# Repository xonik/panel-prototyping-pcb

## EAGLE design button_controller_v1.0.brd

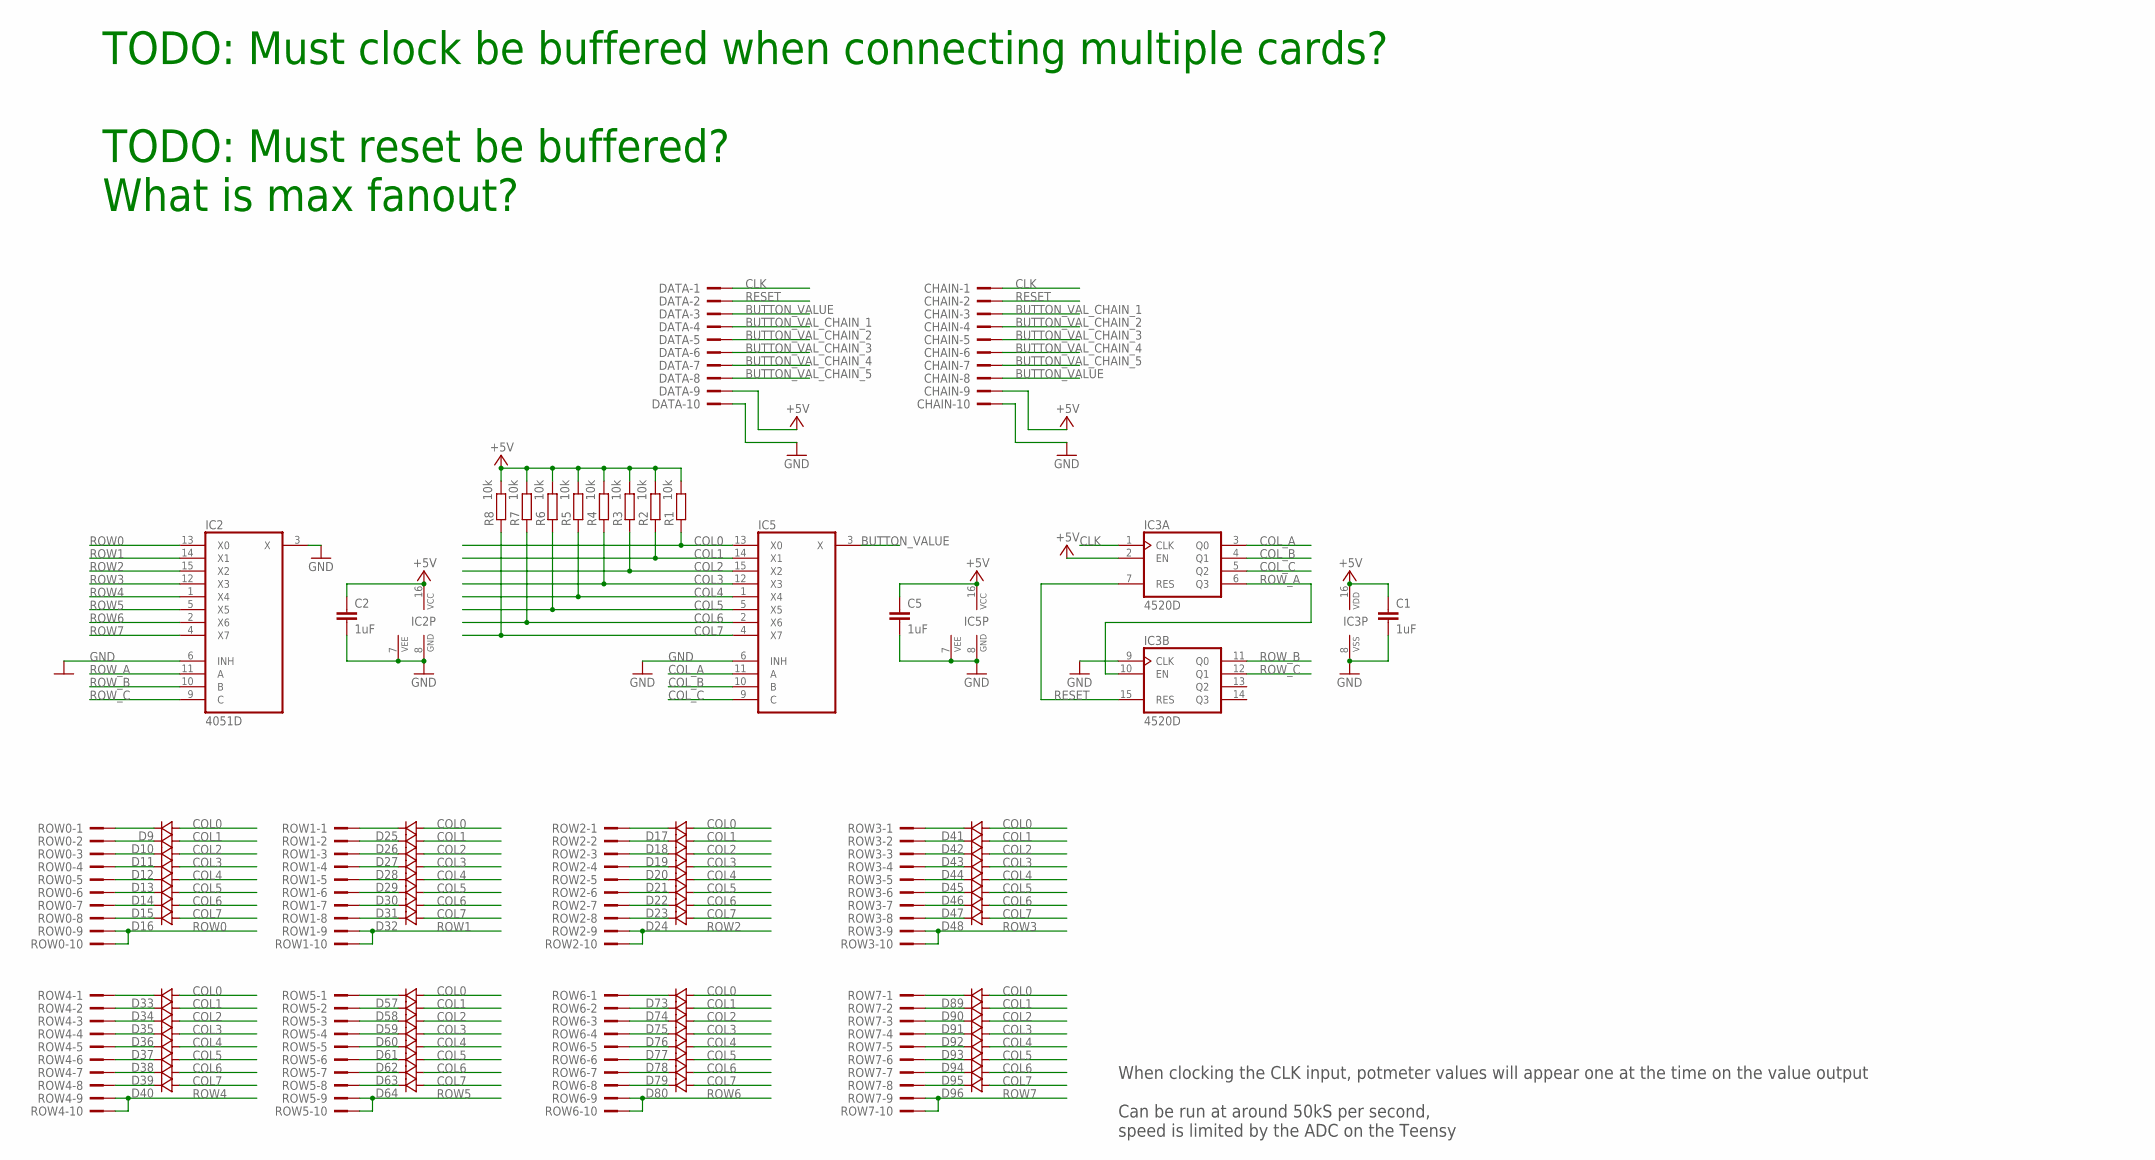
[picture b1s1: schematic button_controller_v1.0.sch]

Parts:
C1, C2, C5: 1uF; C0603-J
CHAIN: CONN-IDC-10PS; CONN-IDC10P-S
D9, D10, D11, D12, D13, D14, D15, D16, D17, D18, D19, D20, D21, D22, D23, D24, D25, D26, D27, D28, D29, D30, D31, D32, D33, D34, D35, D36, D37, D38, D39, D40, D41, D42, D43, D44, D45, D46, D47, D48, D57, D58, D59, D60, D61, D62, D63, D64, D73, D74, D75, D76, D77, D78, D79, D80, D89, D90, D91, D92, D93, D94, D95, D96: 1N4148SOD323; SOD323J
DATA: CONN-IDC-10PS; CONN-IDC10P-S
IC2, IC5: 4051D; SO16
IC3: 4520D; SO16
R1, R2, R3, R4, R5, R6, R7, R8: 10k; R0603
ROW0, ROW1, ROW2, ROW3, ROW4, ROW5, ROW6, ROW7: CONN-IDC-10PS; CONN-IDC10P-S

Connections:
+5V: C1.1, C2.1, C5.1, CHAIN.9, DATA.9, IC2.16 (VCC), IC3.2 (EN), IC3.16 (VDD), IC5.16 (VCC), R1.2, R2.2, R3.2, R4.2, R5.2, R6.2, R7.2, R8.2
BUTTON_VALUE: CHAIN.8, DATA.3, IC5.3 (X)
BUTTON_VAL_CHAIN_1: CHAIN.3, DATA.4
BUTTON_VAL_CHAIN_2: CHAIN.4, DATA.5
BUTTON_VAL_CHAIN_3: CHAIN.5, DATA.6
BUTTON_VAL_CHAIN_4: CHAIN.6, DATA.7
BUTTON_VAL_CHAIN_5: CHAIN.7, DATA.8
CLK: CHAIN.1, DATA.1, IC3.1 (CLK)
COL0: D9.2 (A), D17.2 (A), D25.2 (A), D33.2 (A), D41.2 (A), D57.2 (A), D73.2 (A), D89.2 (A), IC5.13 (X0), R1.1
COL1: D10.2 (A), D18.2 (A), D26.2 (A), D34.2 (A), D42.2 (A), D58.2 (A), D74.2 (A), D90.2 (A), IC5.14 (X1), R2.1
COL2: D11.2 (A), D19.2 (A), D27.2 (A), D35.2 (A), D43.2 (A), D59.2 (A), D75.2 (A), D91.2 (A), IC5.15 (X2), R3.1
COL3: D12.2 (A), D20.2 (A), D28.2 (A), D36.2 (A), D44.2 (A), D60.2 (A), D76.2 (A), D92.2 (A), IC5.12 (X3), R4.1
COL4: D13.2 (A), D21.2 (A), D29.2 (A), D37.2 (A), D45.2 (A), D61.2 (A), D77.2 (A), D93.2 (A), IC5.1 (X4), R5.1
COL5: D14.2 (A), D22.2 (A), D30.2 (A), D38.2 (A), D46.2 (A), D62.2 (A), D78.2 (A), D94.2 (A), IC5.5 (X5), R6.1
COL6: D15.2 (A), D23.2 (A), D31.2 (A), D39.2 (A), D47.2 (A), D63.2 (A), D79.2 (A), D95.2 (A), IC5.2 (X6), R7.1
COL7: D16.2 (A), D24.2 (A), D32.2 (A), D40.2 (A), D48.2 (A), D64.2 (A), D80.2 (A), D96.2 (A), IC5.4 (X7), R8.1
COL_A: IC3.3 (Q0), IC5.11 (A)
COL_B: IC3.4 (Q1), IC5.10 (B)
COL_C: IC3.5 (Q2), IC5.9 (C)
GND: C1.2, C2.2, C5.2, CHAIN.10, DATA.10, IC2.3 (X), IC2.6 (INH), IC2.7 (VEE), IC2.8 (GND), IC3.8 (VSS), IC3.9 (CLK), IC5.6 (INH), IC5.7 (VEE), IC5.8 (GND)
unnamed: D9.1 (C), ROW0.1
unnamed: D10.1 (C), ROW0.2
unnamed: D11.1 (C), ROW0.3
unnamed: D12.1 (C), ROW0.4
unnamed: D13.1 (C), ROW0.5
unnamed: D14.1 (C), ROW0.6
unnamed: D15.1 (C), ROW0.7
unnamed: D16.1 (C), ROW0.8
unnamed: D17.1 (C), ROW2.1
unnamed: D18.1 (C), ROW2.2
unnamed: D19.1 (C), ROW2.3
unnamed: D20.1 (C), ROW2.4
unnamed: D21.1 (C), ROW2.5
unnamed: D22.1 (C), ROW2.6
unnamed: D23.1 (C), ROW2.7
unnamed: D24.1 (C), ROW2.8
unnamed: D25.1 (C), ROW1.1
unnamed: D26.1 (C), ROW1.2
unnamed: D27.1 (C), ROW1.3
unnamed: D28.1 (C), ROW1.4
unnamed: D29.1 (C), ROW1.5
unnamed: D30.1 (C), ROW1.6
unnamed: D31.1 (C), ROW1.7
unnamed: D32.1 (C), ROW1.8
unnamed: D33.1 (C), ROW4.1
unnamed: D34.1 (C), ROW4.2
unnamed: D35.1 (C), ROW4.3
unnamed: D36.1 (C), ROW4.4
unnamed: D37.1 (C), ROW4.5
unnamed: D38.1 (C), ROW4.6
unnamed: D39.1 (C), ROW4.7
unnamed: D40.1 (C), ROW4.8
unnamed: D41.1 (C), ROW3.1
unnamed: D42.1 (C), ROW3.2
unnamed: D43.1 (C), ROW3.3
unnamed: D44.1 (C), ROW3.4
unnamed: D45.1 (C), ROW3.5
unnamed: D46.1 (C), ROW3.6
unnamed: D47.1 (C), ROW3.7
unnamed: D48.1 (C), ROW3.8
unnamed: D57.1 (C), ROW5.1
unnamed: D58.1 (C), ROW5.2
unnamed: D59.1 (C), ROW5.3
unnamed: D60.1 (C), ROW5.4
unnamed: D61.1 (C), ROW5.5
unnamed: D62.1 (C), ROW5.6
unnamed: D63.1 (C), ROW5.7
unnamed: D64.1 (C), ROW5.8
unnamed: D73.1 (C), ROW6.1
unnamed: D74.1 (C), ROW6.2
unnamed: D75.1 (C), ROW6.3
unnamed: D76.1 (C), ROW6.4
unnamed: D77.1 (C), ROW6.5
unnamed: D78.1 (C), ROW6.6
unnamed: D79.1 (C), ROW6.7
unnamed: D80.1 (C), ROW6.8
unnamed: D89.1 (C), ROW7.1
unnamed: D90.1 (C), ROW7.2
unnamed: D91.1 (C), ROW7.3
unnamed: D92.1 (C), ROW7.4
unnamed: D93.1 (C), ROW7.5
unnamed: D94.1 (C), ROW7.6
unnamed: D95.1 (C), ROW7.7
unnamed: D96.1 (C), ROW7.8
RESET: CHAIN.2, DATA.2, IC3.7 (RES), IC3.15 (RES)
ROW0: IC2.13 (X0), ROW0.9, ROW0.10
ROW1: IC2.14 (X1), ROW1.9, ROW1.10
ROW2: IC2.15 (X2), ROW2.9, ROW2.10
ROW3: IC2.12 (X3), ROW3.9, ROW3.10
ROW4: IC2.1 (X4), ROW4.9, ROW4.10
ROW5: IC2.5 (X5), ROW5.9, ROW5.10
ROW6: IC2.2 (X6), ROW6.9, ROW6.10
ROW7: IC2.4 (X7), ROW7.9, ROW7.10
ROW_A: IC2.11 (A), IC3.6 (Q3), IC3.10 (EN)
ROW_B: IC2.10 (B), IC3.11 (Q0)
ROW_C: IC2.9 (C), IC3.12 (Q1)

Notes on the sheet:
When clocking the CLK input, potmeter values will appear one at the time on the value output Can be run at around 50kS per second, speed is limited by the ADC on the Teensy
TODO: Must clock be buffered when connecting multiple cards? TODO: Must reset be buffered? What is max fanout?

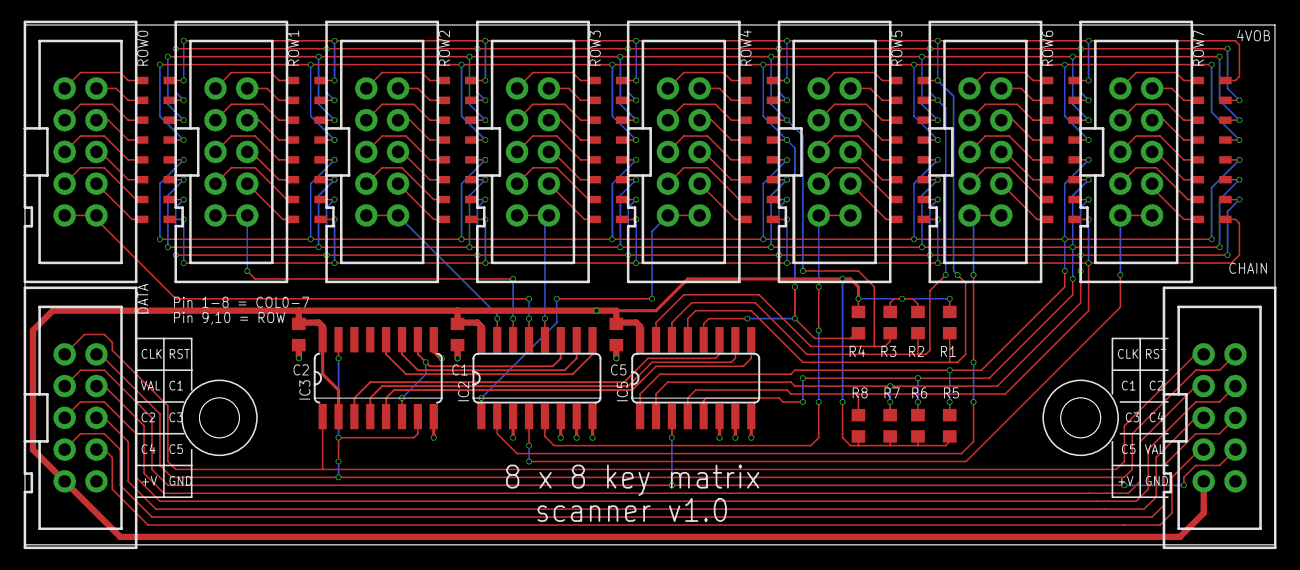
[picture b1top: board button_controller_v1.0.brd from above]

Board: 2 copper layers, 100.0 x 41.6 mm, 89 parts (1 on the bottom side), 96 nets.

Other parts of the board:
U$1: XONIK_LOGO_60

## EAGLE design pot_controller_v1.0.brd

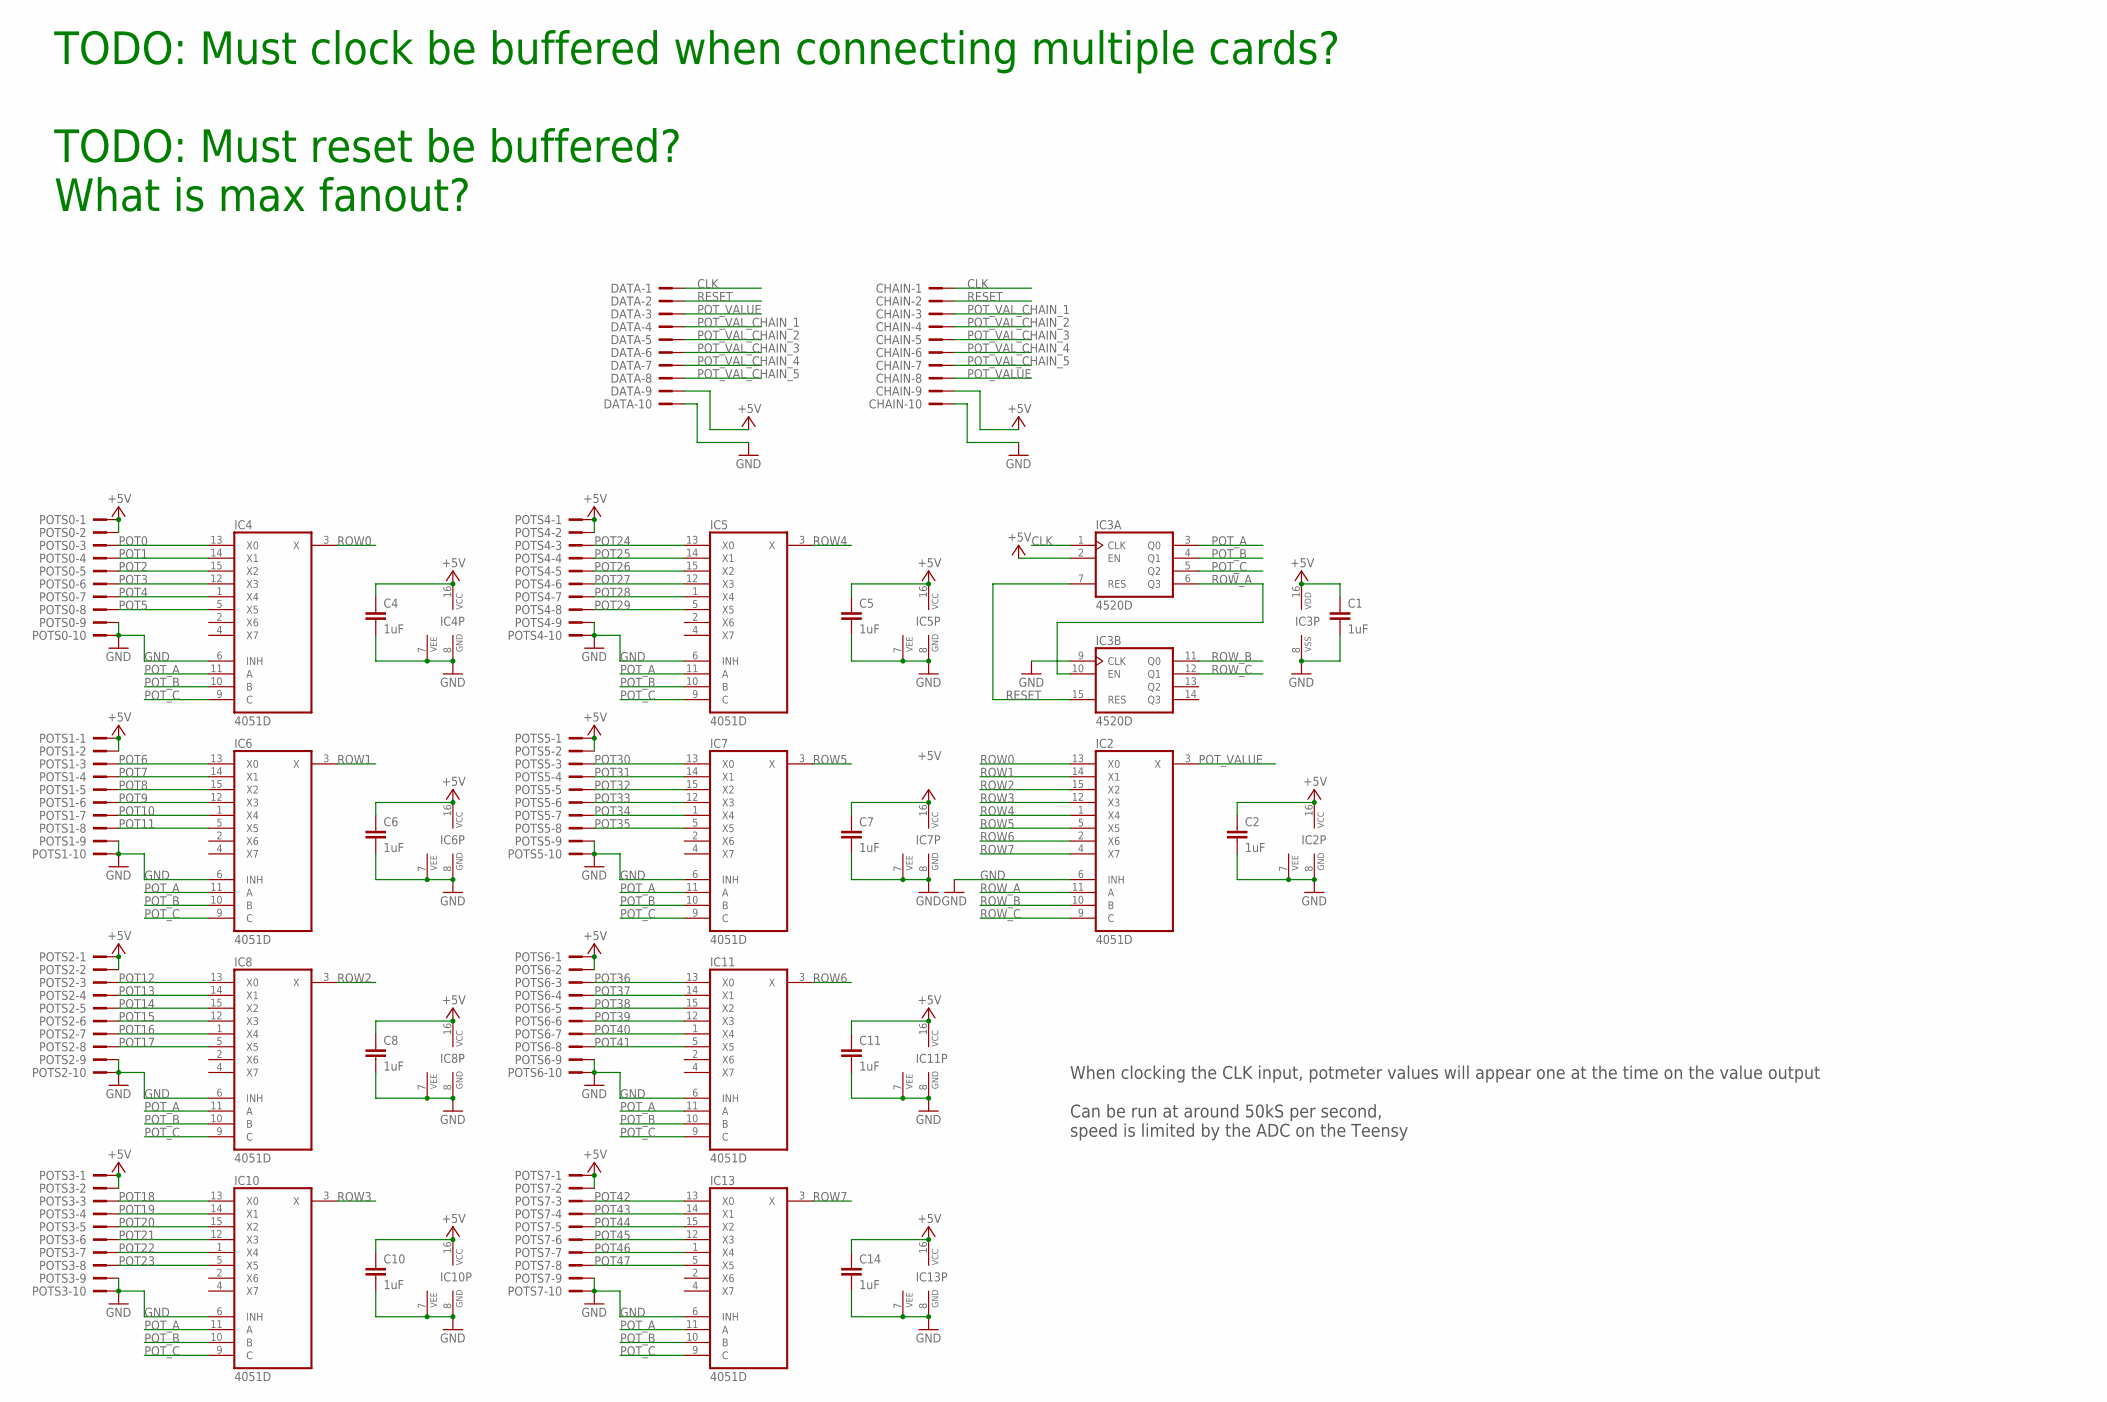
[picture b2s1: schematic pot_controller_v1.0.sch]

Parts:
C1, C2, C4, C5, C6, C7, C8, C10, C11, C14: 1uF; C0603-J
CHAIN: CONN-IDC-10PS; CONN-IDC10P-S
DATA: CONN-IDC-10PS; CONN-IDC10P-S
IC2, IC4, IC5, IC6, IC7, IC8, IC10, IC11, IC13: 4051D; SO16
IC3: 4520D; SO16
POTS0, POTS1, POTS2, POTS3, POTS4, POTS5, POTS6, POTS7: CONN-IDC-10PS; CONN-IDC10P-S

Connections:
+5V: C1.1, C2.1, C4.1, C5.1, C6.1, C7.1, C8.1, C10.1, C11.1, C14.1, CHAIN.9, DATA.9, IC2.16 (VCC), IC3.2 (EN), IC3.16 (VDD), IC4.16 (VCC), IC5.16 (VCC), IC6.16 (VCC), IC7.16 (VCC), IC8.16 (VCC), IC10.16 (VCC), IC11.16 (VCC), IC13.16 (VCC), POTS0.1, POTS0.2, POTS1.1, POTS1.2, POTS2.1, POTS2.2, POTS3.1, POTS3.2, POTS4.1, POTS4.2, POTS5.1, POTS5.2, POTS6.1, POTS6.2, POTS7.1, POTS7.2
CLK: CHAIN.1, DATA.1, IC3.1 (CLK)
GND: C1.2, C2.2, C4.2, C5.2, C6.2, C7.2, C8.2, C10.2, C11.2, C14.2, CHAIN.10, DATA.10, IC2.6 (INH), IC2.7 (VEE), IC2.8 (GND), IC3.8 (VSS), IC3.9 (CLK), IC4.6 (INH), IC4.7 (VEE), IC4.8 (GND), IC5.6 (INH), IC5.7 (VEE), IC5.8 (GND), IC6.6 (INH), IC6.7 (VEE), IC6.8 (GND), IC7.6 (INH), IC7.7 (VEE), IC7.8 (GND), IC8.6 (INH), IC8.7 (VEE), IC8.8 (GND), IC10.6 (INH), IC10.7 (VEE), IC10.8 (GND), IC11.6 (INH), IC11.7 (VEE), IC11.8 (GND), IC13.6 (INH), IC13.7 (VEE), IC13.8 (GND), POTS0.9, POTS0.10, POTS1.9, POTS1.10, POTS2.9, POTS2.10, POTS3.9, POTS3.10, POTS4.9, POTS4.10, POTS5.9, POTS5.10, POTS6.9, POTS6.10, POTS7.9, POTS7.10
POT0: IC4.13 (X0), POTS0.3
POT1: IC4.14 (X1), POTS0.4
POT2: IC4.15 (X2), POTS0.5
POT3: IC4.12 (X3), POTS0.6
POT4: IC4.1 (X4), POTS0.7
POT5: IC4.5 (X5), POTS0.8
POT6: IC6.13 (X0), POTS1.3
POT7: IC6.14 (X1), POTS1.4
POT8: IC6.15 (X2), POTS1.5
POT9: IC6.12 (X3), POTS1.6
POT10: IC6.1 (X4), POTS1.7
POT11: IC6.5 (X5), POTS1.8
POT12: IC8.13 (X0), POTS2.3
POT13: IC8.14 (X1), POTS2.4
POT14: IC8.15 (X2), POTS2.5
POT15: IC8.12 (X3), POTS2.6
POT16: IC8.1 (X4), POTS2.7
POT17: IC8.5 (X5), POTS2.8
POT18: IC10.13 (X0), POTS3.3
POT19: IC10.14 (X1), POTS3.4
POT20: IC10.15 (X2), POTS3.5
POT21: IC10.12 (X3), POTS3.6
POT22: IC10.1 (X4), POTS3.7
POT23: IC10.5 (X5), POTS3.8
POT24: IC5.13 (X0), POTS4.3
POT25: IC5.14 (X1), POTS4.4
POT26: IC5.15 (X2), POTS4.5
POT27: IC5.12 (X3), POTS4.6
POT28: IC5.1 (X4), POTS4.7
POT29: IC5.5 (X5), POTS4.8
POT30: IC7.13 (X0), POTS5.3
POT31: IC7.14 (X1), POTS5.4
POT32: IC7.15 (X2), POTS5.5
POT33: IC7.12 (X3), POTS5.6
POT34: IC7.1 (X4), POTS5.7
POT35: IC7.5 (X5), POTS5.8
POT36: IC11.13 (X0), POTS6.3
POT37: IC11.14 (X1), POTS6.4
POT38: IC11.15 (X2), POTS6.5
POT39: IC11.12 (X3), POTS6.6
POT40: IC11.1 (X4), POTS6.7
POT41: IC11.5 (X5), POTS6.8
POT42: IC13.13 (X0), POTS7.3
POT43: IC13.14 (X1), POTS7.4
POT44: IC13.15 (X2), POTS7.5
POT45: IC13.12 (X3), POTS7.6
POT46: IC13.1 (X4), POTS7.7
POT47: IC13.5 (X5), POTS7.8
POT_A: IC3.3 (Q0), IC4.11 (A), IC5.11 (A), IC6.11 (A), IC7.11 (A), IC8.11 (A), IC10.11 (A), IC11.11 (A), IC13.11 (A)
POT_B: IC3.4 (Q1), IC4.10 (B), IC5.10 (B), IC6.10 (B), IC7.10 (B), IC8.10 (B), IC10.10 (B), IC11.10 (B), IC13.10 (B)
POT_C: IC3.5 (Q2), IC4.9 (C), IC5.9 (C), IC6.9 (C), IC7.9 (C), IC8.9 (C), IC10.9 (C), IC11.9 (C), IC13.9 (C)
POT_VALUE: CHAIN.8, DATA.3, IC2.3 (X)
POT_VAL_CHAIN_1: CHAIN.3, DATA.4
POT_VAL_CHAIN_2: CHAIN.4, DATA.5
POT_VAL_CHAIN_3: CHAIN.5, DATA.6
POT_VAL_CHAIN_4: CHAIN.6, DATA.7
POT_VAL_CHAIN_5: CHAIN.7, DATA.8
RESET: CHAIN.2, DATA.2, IC3.7 (RES), IC3.15 (RES)
ROW0: IC2.13 (X0), IC4.3 (X)
ROW1: IC2.14 (X1), IC6.3 (X)
ROW2: IC2.15 (X2), IC8.3 (X)
ROW3: IC2.12 (X3), IC10.3 (X)
ROW4: IC2.1 (X4), IC5.3 (X)
ROW5: IC2.5 (X5), IC7.3 (X)
ROW6: IC2.2 (X6), IC11.3 (X)
ROW7: IC2.4 (X7), IC13.3 (X)
ROW_A: IC2.11 (A), IC3.6 (Q3), IC3.10 (EN)
ROW_B: IC2.10 (B), IC3.11 (Q0)
ROW_C: IC2.9 (C), IC3.12 (Q1)

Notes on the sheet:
When clocking the CLK input, potmeter values will appear one at the time on the value output Can be run at around 50kS per second, speed is limited by the ADC on the Teensy
TODO: Must clock be buffered when connecting multiple cards? TODO: Must reset be buffered? What is max fanout?

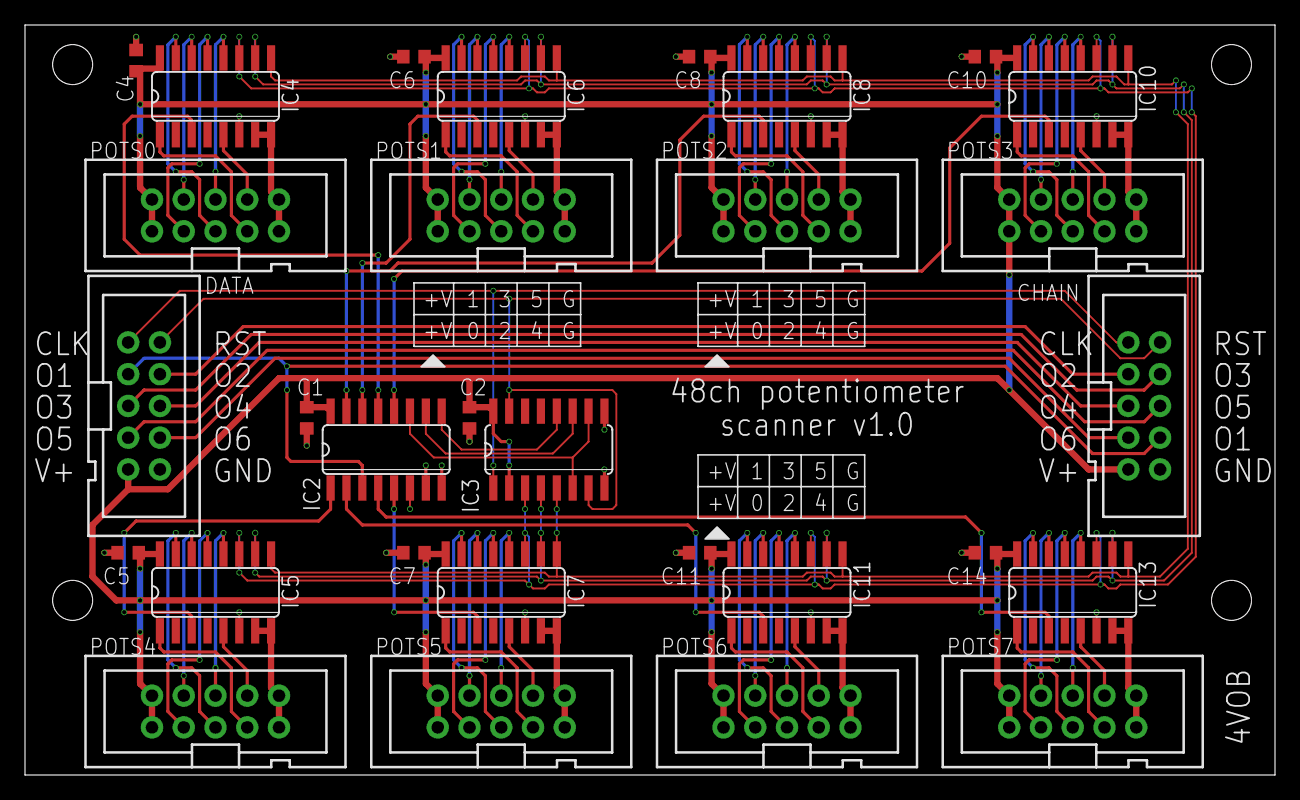
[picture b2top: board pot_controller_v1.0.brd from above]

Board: 2 copper layers, 100.0 x 60.0 mm, 31 parts (1 on the bottom side), 72 nets.

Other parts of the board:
U$1: XONIK_LOGO_60

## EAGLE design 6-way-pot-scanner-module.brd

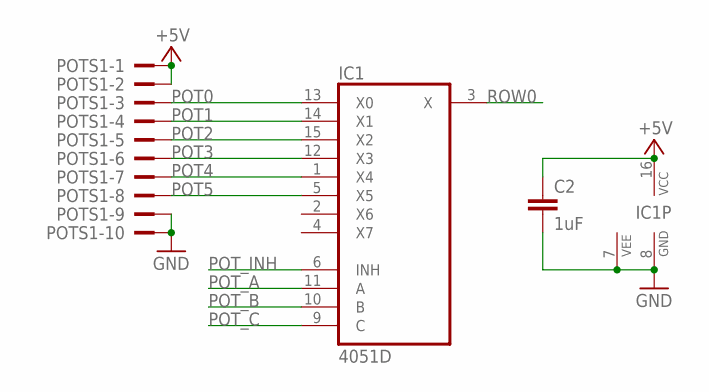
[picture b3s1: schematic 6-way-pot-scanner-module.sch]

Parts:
C2: 1uF; C0603-J
IC1: 4051D; SO16
POTS1: CONN-IDC-10PS; CONN-IDC10P-S

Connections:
+5V: C2.1, IC1.16 (VCC), POTS1.1, POTS1.2
GND: C2.2, IC1.7 (VEE), IC1.8 (GND), POTS1.9, POTS1.10
POT0: IC1.13 (X0), POTS1.3
POT1: IC1.14 (X1), POTS1.4
POT2: IC1.15 (X2), POTS1.5
POT3: IC1.12 (X3), POTS1.6
POT4: IC1.1 (X4), POTS1.7
POT5: IC1.5 (X5), POTS1.8
POT_A: IC1.11 (A)
POT_B: IC1.10 (B)
POT_C: IC1.9 (C)
POT_INH: IC1.6 (INH)
ROW0: IC1.3 (X)

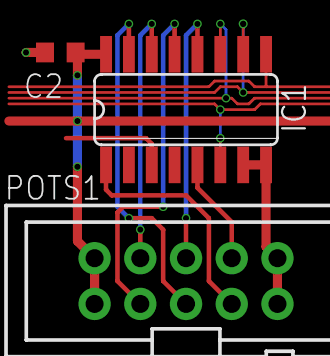
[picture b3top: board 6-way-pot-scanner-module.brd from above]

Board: 2 copper layers, 3 parts (0 on the bottom side), 8 nets.

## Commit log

2025-01-01 First version, missing silk, testing etc
2025-01-02 Fixed routing except for possible inhibit-removal
2025-01-02 Added silk screen
2025-01-02 Added scanner module
2025-01-02 Removed temp files
2025-01-06 First try at 64 channel button matrix
2025-01-06 Finished tracing
2025-01-07 Massive rerouting for a clearer separation between x and y direction
2025-01-07 As small as it gets
2025-01-07 Finished everything
2025-01-07 Added v1.0 of matrix splitter
2025-01-07 Fixed v1.1 of button breakout (SMD version)
2025-01-08 Updated IDC connector
2025-01-08 Updated IDC connector size
2025-01-08 Added usage comment
